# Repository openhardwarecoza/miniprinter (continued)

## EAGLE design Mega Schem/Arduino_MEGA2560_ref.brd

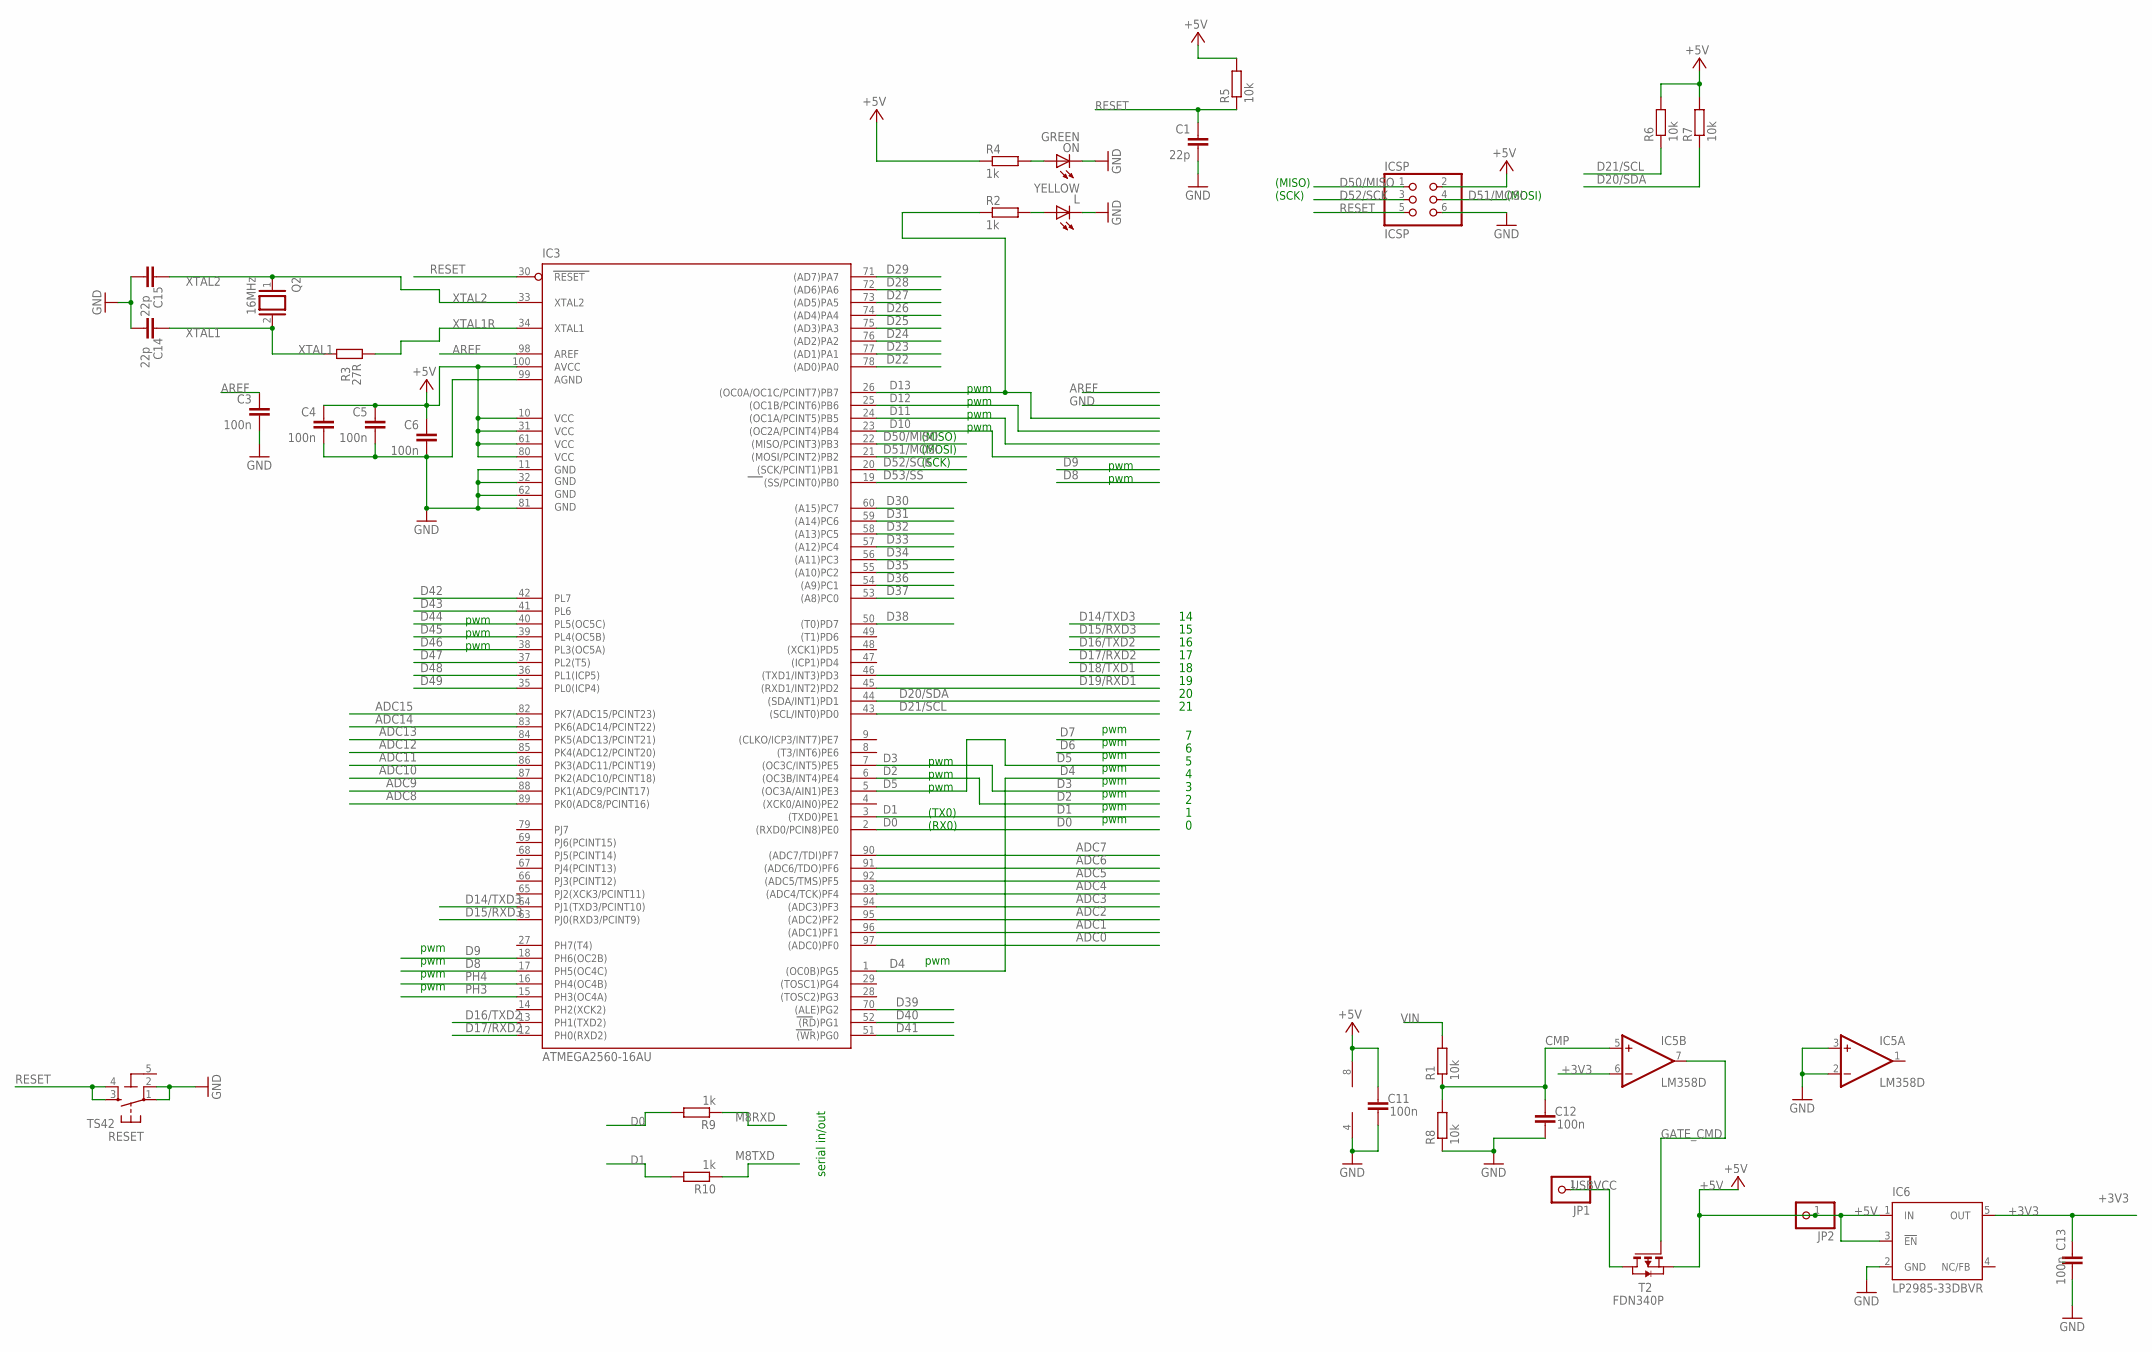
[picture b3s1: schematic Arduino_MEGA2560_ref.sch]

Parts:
C1, C14, C15: 22p; C0603-ROUND
C3, C4, C5, C6, C12, C13: 100n; C0603-ROUND
C11: 100n; C0603
IC3: ATMEGA2560-16AU; TQFP100
IC5: LM358D; SO08
IC6: LP2985-33DBVR; SOT23-DBV
ICSP: ICSP; 2X03
JP1, JP2: PINHD-1X1; 1X01
L: YELLOW; CHIP-LED0805
ON: GREEN; CHIP-LED0805
Q2: 16MHz; QS
R1, R5, R6, R7, R8: 10k; R0603
R2, R4, R9, R10: 1k; R0603
R3: 27R; R0603-ROUND
RESET: TS42
T2: FDN340P; SOT-23

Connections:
5-GND: RESET.5 (5-GND)
+3V3: C13.2, IC5.6 (-IN), IC6.5 (OUT)
+5V: C4.1, C5.1, C6.1, C11.2, IC3.10 (VCC), IC3.31 (VCC1), IC3.61 (VCC2), IC3.80 (VCC3), IC3.100 (AVCC), IC5.8 (V+), IC6.1 (IN), IC6.3 (!EN), ICSP.2, JP2.1, R4.1, R5.2, R6.2, R7.2, T2.2 (S)
ADC0: IC3.97 ((ADC0)PF0)
ADC1: IC3.96 ((ADC1)PF1)
ADC2: IC3.95 ((ADC2)PF2)
ADC3: IC3.94 ((ADC3)PF3)
ADC4: IC3.93 ((ADC4/TCK)PF4)
ADC5: IC3.92 ((ADC5/TMS)PF5)
ADC6: IC3.91 ((ADC6/TDO)PF6)
ADC7: IC3.90 ((ADC7/TDI)PF7)
ADC8: IC3.89 (PK0(ADC8/PCINT16))
ADC9: IC3.88 (PK1(ADC9/PCINT17))
ADC10: IC3.87 (PK2(ADC10/PCINT18))
ADC11: IC3.86 (PK3(ADC11/PCINT19))
ADC12: IC3.85 (PK4(ADC12/PCINT20))
ADC13: IC3.84 (PK5(ADC13/PCINT21))
ADC14: IC3.83 (PK6(ADC14/PCINT22))
ADC15: IC3.82 (PK7(ADC15/PCINT23))
AREF: C3.1, IC3.98 (AREF)
CMP: C12.2, IC5.5 (+IN), R1.1, R8.2
D0: IC3.2 ((RXD0/PCIN8)PE0), R9.2
D1: IC3.3 ((TXD0)PE1), R10.2
D2: IC3.6 ((OC3B/INT4)PE4)
D3: IC3.7 ((OC3C/INT5)PE5)
D4: IC3.1 ((OC0B)PG5)
D5: IC3.5 ((OC3A/AIN1)PE3)
D8: IC3.17 (PH5(OC4C))
D9: IC3.18 (PH6(OC2B))
D10: IC3.23 ((OC2A/PCINT4)PB4)
D11: IC3.24 ((OC1A/PCINT5)PB5)
D12: IC3.25 ((OC1B/PCINT6)PB6)
D13: IC3.26 ((OC0A/OC1C/PCINT7)PB7), R2.1
D14/TXD3: IC3.64 (PJ1(TXD3/PCINT10))
D15/RXD3: IC3.63 (PJ0(RXD3/PCINT9))
D16/TXD2: IC3.13 (PH1(TXD2))
D17/RXD2: IC3.12 (PH0(RXD2))
D18/TXD1: IC3.46 ((TXD1/INT3)PD3)
D19/RXD1: IC3.45 ((RXD1/INT2)PD2)
D20/SDA: IC3.44 ((SDA/INT1)PD1), R7.1
D21/SCL: IC3.43 ((SCL/INT0)PD0), R6.1
D22: IC3.78 ((AD0)PA0)
D23: IC3.77 ((AD1)PA1)
D24: IC3.76 ((AD2)PA2)
D25: IC3.75 ((AD3)PA3)
D26: IC3.74 ((AD4)PA4)
D27: IC3.73 ((AD5)PA5)
D28: IC3.72 ((AD6)PA6)
D29: IC3.71 ((AD7)PA7)
D30: IC3.60 ((A15)PC7)
D31: IC3.59 ((A14)PC6)
D32: IC3.58 ((A13)PC5)
D33: IC3.57 ((A12)PC4)
D34: IC3.56 ((A11)PC3)
D35: IC3.55 ((A10)PC2)
D36: IC3.54 ((A9)PC1)
D37: IC3.53 ((A8)PC0)
D38: IC3.50 ((T0)PD7)
D39: IC3.70 ((ALE)PG2)
D40: IC3.52 ((RD)PG1)
D41: IC3.51 ((WR)PG0)
D42: IC3.42 (PL7)
D43: IC3.41 (PL6)
D44: IC3.40 (PL5(OC5C))
D45: IC3.39 (PL4(OC5B))
D46: IC3.38 (PL3(OC5A))
D47: IC3.37 (PL2(T5))
D48: IC3.36 (PL1(ICP5))
D49: IC3.35 (PL0(ICP4))
D50/MISO: IC3.22 ((MISO/PCINT3)PB3), ICSP.1
D51/MOSI: IC3.21 ((MOSI/PCINT2)PB2), ICSP.4
D52/SCK: IC3.20 ((SCK/PCINT1)PB1), ICSP.3
D53/SS: IC3.19 ((SS/PCINT0)PB0)
GATE_CMD: IC5.7 (OUT), T2.3 (G)
GND: C1.2, C3.2, C4.2, C5.2, C6.2, C11.1, C12.1, C13.1, C14.1, C15.1, IC3.11 (GND), IC3.32 (GND1), IC3.62 (GND2), IC3.81 (GND3), IC3.99 (AGND), IC5.2 (-IN), IC5.3 (+IN), IC5.4 (V-), IC6.2 (GND), ICSP.6, L.C, ON.C, R8.1, RESET.1, RESET.2
M8RXD: R9.1
M8TXD: R10.1
unnamed: L.A, R2.2
unnamed: ON.A, R4.2
PH3: IC3.15 (PH3(OC4A))
PH4: IC3.16 (PH4(OC4B))
RESET: C1.1, IC3.30 (RESET), ICSP.5, R5.1, RESET.3, RESET.4
USBVCC: JP1.1, T2.1 (D)
VIN: R1.2
XTAL1: C14.2, Q2.2, R3.2
XTAL1R: IC3.34 (XTAL1), R3.1
XTAL2: C15.2, IC3.33 (XTAL2), Q2.1

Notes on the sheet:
(SCK)
(MISO)
(MOSI)
pwm
(TX0)
(RX0)
serial in/out

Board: 2 copper layers, 31 parts (0 on the bottom side), 21 nets, no tracks yet.

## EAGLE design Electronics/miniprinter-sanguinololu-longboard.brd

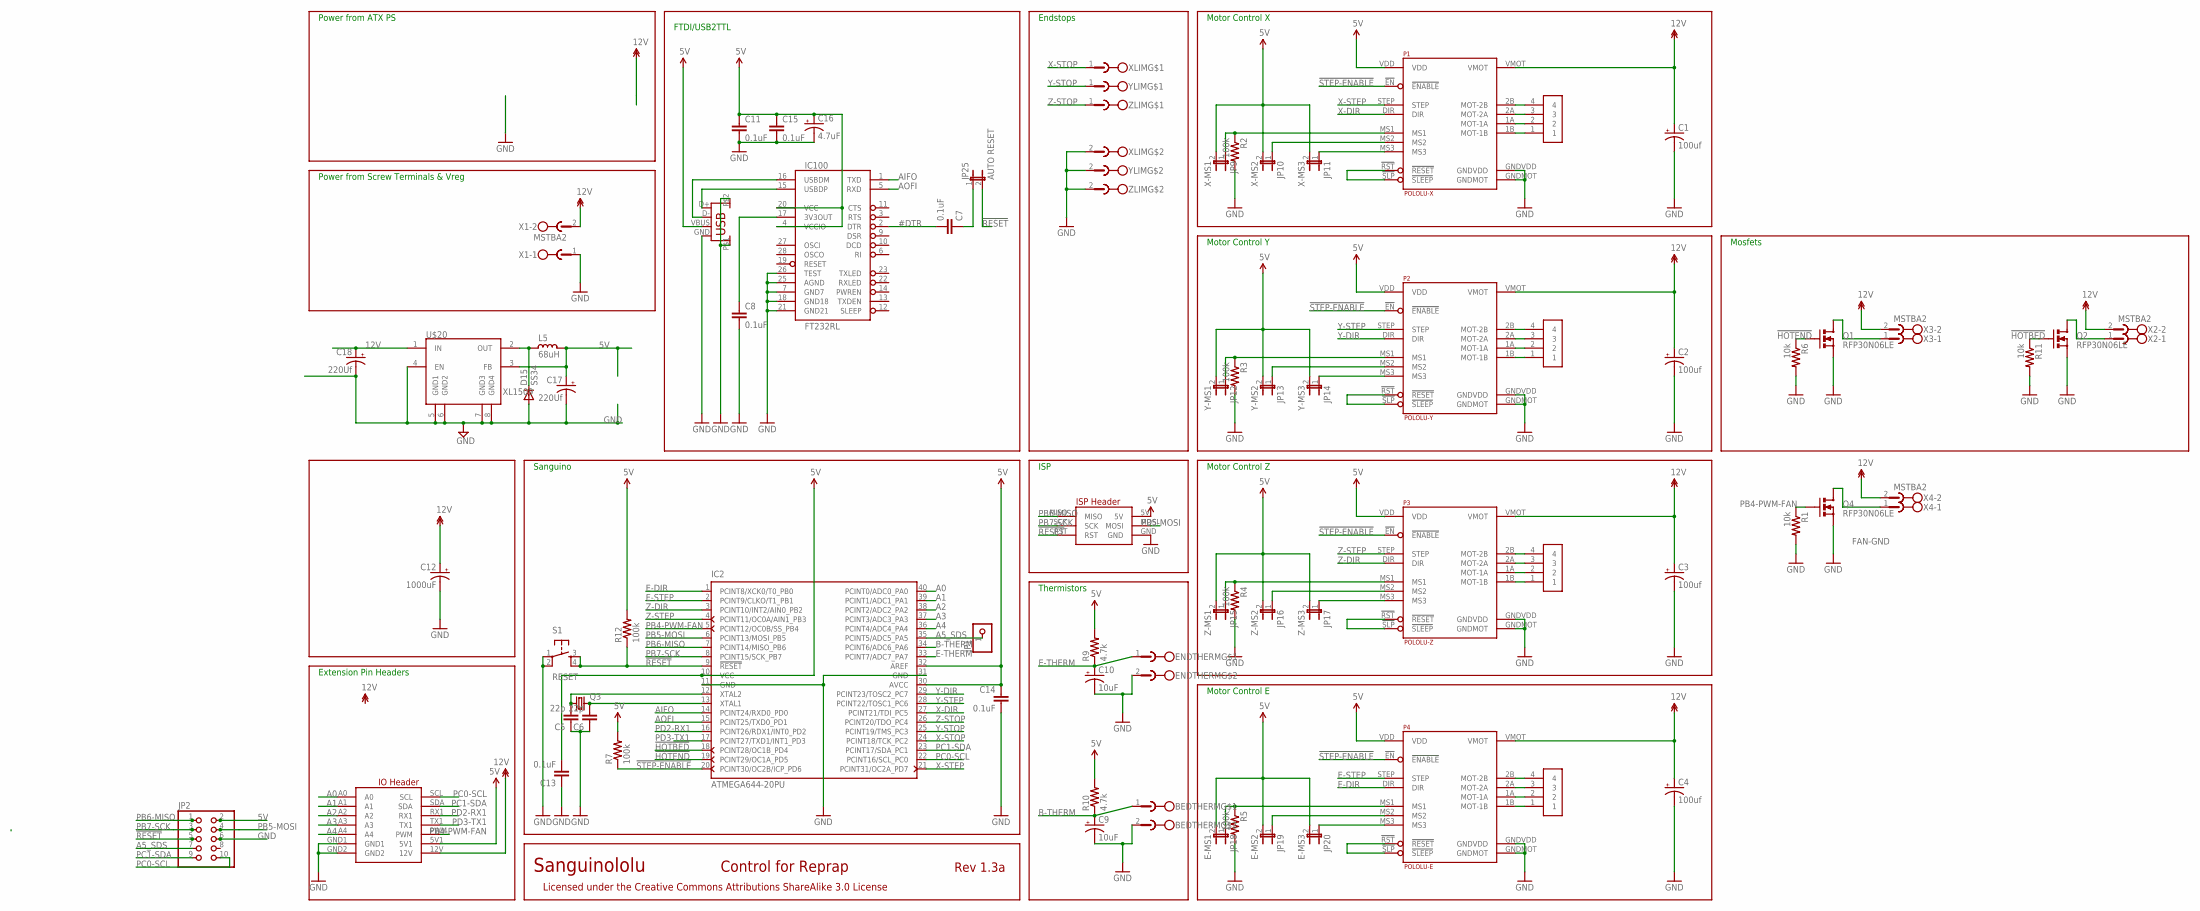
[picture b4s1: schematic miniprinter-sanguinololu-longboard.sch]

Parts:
BEDTHERM: Phoenix Pluggable 3.81mm 2 way; MC1.5/2-G-3.81
C1, C2, C3, C4: 100uf; CPOL-RADIAL-100UF-25V
C5, C6: 22p; CAP-PTH-SMALL2
C7, C8, C11, C13, C14, C15: 0.1uF; CAP-PTH-SMALL2
C9, C10: 10uF; CPOL-RADIAL-10UF-25V
C12: 1000uF; CPOL-RADIAL-1000UF-25V
C16: 4.7uF; CPOL-RADIAL-10UF-25V
C17, C18: 220Uf; CPOL-RADIAL-100UF-25V
D15: SS34; DO-214AC
ENDTHERM: Phoenix Pluggable 3.81mm 2 way; MC1.5/2-G-3.81
IC2: ATMEGA644-20PU; DIL40
IC100: FT232RL; SSOP28DB
J1: USB; USB-B-PTH
JP1: PINHD-1X1; 1X01
JP2: PINHD-2X5; 2X05
JP9: X-MS1; 1X02
JP10: X-MS2; 1X02
JP11: X-MS3; 1X02
JP12: Y-MS1; 1X02
JP13: Y-MS2; 1X02
JP14: Y-MS3; 1X02
JP15: Z-MS1; 1X02
JP16: Z-MS2; 1X02
JP17: Z-MS3; 1X02
JP18: E-MS1; 1X02
JP19: E-MS2; 1X02
JP20: E-MS3; 1X02
JP25: AUTO RESET; 1X02
L5: 68uH; CD75
P1: POLOLU-X; POLOLU-ALLEGRO-PTH
P2: POLOLU-Y; POLOLU-ALLEGRO-PTH
P3: POLOLU-Z; POLOLU-ALLEGRO-PTH
P4: POLOLU-E; POLOLU-ALLEGRO-PTH
Q1, Q2, Q4: RFP30N06LE; TO220V
Q3: CRYSTALHC49S; HC49/S
R1, R6, R11: 10k; AXIAL-0.3
R2, R3, R4, R5, R7, R12: 100k; AXIAL-0.3
R9, R10: 4.7k; AXIAL-0.3
S1: RESET; TACTILE-PTH
U$17, U$25, U$26, U$27: CONNECTOR-M4; 3.81MM-4WAY-PLUGGABLE-SCREW
U$20: XL1509; SO08
U$24: IO_HEADERS_SCREW; IO_HEADER-PLATEDSCREW
X1, X2, X3, X4: MSTBA2
XLIM: Phoenix Pluggable 3.81mm 2 way; MC1.5/2-G-3.81
YLIM: Phoenix Pluggable 3.81mm 2 way; MC1.5/2-G-3.81
ZLIM: Phoenix Pluggable 3.81mm 2 way; MC1.5/2-G-3.81

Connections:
3V3: C8.1, IC100.17 (3V3OUT)
5V: C11.1, C13.2, C14.1, C15.1, C16.1 (+), C17.1 (+), IC2.10 (VCC), IC2.30 (AVCC), IC2.32 (AREF), IC100.4 (VCCIO), IC100.20 (VCC), J1.VBUS, JP2.2, JP9.2, JP10.2, JP11.2, JP12.2, JP13.2, JP14.2, JP15.2, JP16.2, JP17.2, JP18.2, JP19.2, JP20.2, L5.1, P1.VDD, P2.VDD, P3.VDD, P4.VDD, R7.P$2 (2), R9.P$2 (2), R10.P$2 (2), R12.P$2 (2), U$20.3 (FB), U$24.5V, U$24.5V1
12V: C1.1 (+), C2.1 (+), C3.1 (+), C4.1 (+), C12.1 (+), C18.1 (+), P1.VMOT, P2.VMOT, P3.VMOT, P4.VMOT, U$20.1 (IN), U$24.12V, X1.2, X2.2, X3.2, X4.2
!FTDI-RESET: C7.1, JP25.1
!HOTBED: IC2.18 (PCINT28/OC1B_PD4), Q2.1 (G), R11.P$1 (1)
!HOTEND: IC2.19 (PCINT29/OC1A_PD5), Q1.1 (G), R6.P$1 (1)
!RESET: IC2.9 (!RESET), JP2.5, JP25.2, R12.P$1 (1), S1.3, S1.4, U$24.RST
!STEP-ENABLE: IC2.20 (PCINT30/OC2B/ICP_PD6), P1.!EN (!ENABLE), P2.!EN (!ENABLE), P3.!EN (!ENABLE), P4.!EN (!ENABLE), R7.P$1 (1)
#DTR: C7.2, IC100.2 (DTR)
A0: IC2.40 (PCINT0/ADC0_PA0), U$24.A0
A1: IC2.39 (PCINT1/ADC1_PA1), U$24.A1
A2: IC2.38 (PCINT2/ADC2_PA2), U$24.A2
A3: IC2.37 (PCINT3/ADC3_PA3), U$24.A3
A4: IC2.36 (PCINT4/ADC4_PA4), U$24.A4
A5_SDS: IC2.35 (PCINT5/ADC5_PA5), JP1.1, JP2.7
AIFO: IC2.14 (PCINT24/RXD0_PD0), IC100.1 (TXD)
AOFI: IC2.15 (PCINT25/TXD0_PD1), IC100.5 (RXD)
B-THERM: BEDTHERM.1, C9.1 (+), IC2.34 (PCINT6/ADC6_PA6), R10.P$1 (1)
E-DIR: IC2.1 (PCINT8/XCK0/T0_PB0), P4.DIR
E-MS1: JP18.1, P4.MS1, R5.P$1 (1)
E-MS2: JP19.1, P4.MS2
E-MS3: JP20.1, P4.MS3
E-RESETSLEEP: P4.!RST (!RESET), P4.!SLP (!SLEEP)
E-STEP: IC2.2 (PCINT9/CLKO/T1_PB1), P4.STEP
E-THERM: C10.1 (+), ENDTHERM.1, IC2.33 (PCINT7/ADC7_PA7), R9.P$1 (1)
FAN-GND: Q4.2 (D), X4.1
GND: BEDTHERM.2, C1.2 (-), C2.2 (-), C3.2 (-), C4.2 (-), C5.1, C6.1, C8.2, C9.2 (-), C10.2 (-), C11.2, C12.2 (-), C13.1, C14.2, C15.2, C16.2 (-), C17.2 (-), C18.2 (-), D15.2 (A), ENDTHERM.2, IC2.11 (GND), IC2.31 (GND), IC100.7 (GND7), IC100.18 (GND18), IC100.21 (GND21), IC100.25 (AGND), IC100.26 (TEST), J1.GND, J1.P$1, J1.P$2, JP2.6, P1.GNDMOT, P1.GNDVDD, P2.GNDMOT, P2.GNDVDD, P3.GNDMOT, P3.GNDVDD, P4.GNDMOT, P4.GNDVDD, Q1.3 (S), Q2.3 (S), Q4.3 (S), R1.P$2 (2), R2.P$2 (2), R3.P$2 (2), R4.P$2 (2), R5.P$2 (2), R6.P$2 (2), R11.P$2 (2), S1.1, S1.2, U$20.4 (EN), U$20.5 (GND1), U$20.6 (GND2), U$20.7 (GND3), U$20.8 (GND4), U$24.GND, U$24.GND1, U$24.GND2, X1.1, XLIM.2, YLIM.2, ZLIM.2
HOTBED-GND: Q2.2 (D), X2.1
HOTEND-GND: Q1.2 (D), X3.1
unnamed: P4.1B (MOT-1B), U$27.1
unnamed: P4.1A (MOT-1A), U$27.2
unnamed: P4.2A (MOT-2A), U$27.3
unnamed: P4.2B (MOT-2B), U$27.4
unnamed: P3.1B (MOT-1B), U$26.1
unnamed: P3.1A (MOT-1A), U$26.2
unnamed: P3.2A (MOT-2A), U$26.3
unnamed: P3.2B (MOT-2B), U$26.4
unnamed: P2.1B (MOT-1B), U$25.1
unnamed: P2.1A (MOT-1A), U$25.2
unnamed: P2.2A (MOT-2A), U$25.3
unnamed: P2.2B (MOT-2B), U$25.4
unnamed: P1.1B (MOT-1B), U$17.1
unnamed: P1.1A (MOT-1A), U$17.2
unnamed: P1.2A (MOT-2A), U$17.3
unnamed: P1.2B (MOT-2B), U$17.4
unnamed: D15.1 (C), L5.2, U$20.2 (OUT)
PB4-PWM-FAN: IC2.5 (PCINT12/OC0B/SS_PB4), Q4.1 (G), R1.P$1 (1), U$24.PWM
PB5-MOSI: IC2.6 (PCINT13/MOSI_PB5), JP2.4, U$24.MOSI
PB6-MISO: IC2.7 (PCINT14/MISO_PB6), JP2.1, U$24.MISO
PB7-SCK: IC2.8 (PCINT15/SCK_PB7), JP2.3, U$24.SCK
PC0-SCL: IC2.22 (PCINT16/SCL_PC0), JP2.10, U$24.SCL
PC1-SDA: IC2.23 (PCINT17/SDA_PC1), JP2.9, U$24.SDA
PD2-RX1: IC2.16 (PCINT26/RDX1/INT0_PD2), U$24.RX1
PD3-TX1: IC2.17 (PCINT27/TXD1/INT1_PD3), U$24.TX1
USBDM: IC100.16 (USBDM), J1.D-
USBDP: IC100.15 (USBDP), J1.D+
X-DIR: IC2.27 (PCINT21/TDI_PC5), P1.DIR
X-MS1: JP9.1, P1.MS1, R2.P$1 (1)
X-MS2: JP10.1, P1.MS2
X-MS3: JP11.1, P1.MS3
X-RESETSLEEP: P1.!RST (!RESET), P1.!SLP (!SLEEP)
X-STEP: IC2.21 (PCINT31/OC2A_PD7), P1.STEP
X-STOP: IC2.24 (PCINT18/TCK_PC2), XLIM.1
XTAL1: C6.2, IC2.13 (XTAL1), Q3.2
XTAL2: C5.2, IC2.12 (XTAL2), Q3.1
Y-DIR: IC2.29 (PCINT23/TOSC2_PC7), P2.DIR
Y-MS1: JP12.1, P2.MS1, R3.P$1 (1)
Y-MS2: JP13.1, P2.MS2
Y-MS3: JP14.1, P2.MS3
Y-RESETSLEEP: P2.!RST (!RESET), P2.!SLP (!SLEEP)
Y-STEP: IC2.28 (PCINT22/TOSC1_PC6), P2.STEP
Y-STOP: IC2.25 (PCINT19/TMS_PC3), YLIM.1
Z-DIR: IC2.3 (PCINT10/INT2/AIN0_PB2), P3.DIR
Z-MS1: JP15.1, P3.MS1, R4.P$1 (1)
Z-MS2: JP16.1, P3.MS2
Z-MS3: JP17.1, P3.MS3
Z-RESETSLEEP: P3.!RST (!RESET), P3.!SLP (!SLEEP)
Z-STEP: IC2.4 (PCINT11/OC0A/AIN1_PB3), P3.STEP
Z-STOP: IC2.26 (PCINT20/TDO_PC4), ZLIM.1

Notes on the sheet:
Motor Control X
Motor Control Y
Motor Control Z
Motor Control E
ISP
Thermistors
Endstops
Sanguino
FTDI/USB2TTL
Mosfets
Sanguinololu
Rev 1.3a
Control for Reprap
Licensed under the Creative Commons Attributions ShareAlike 3.0 License
Extension Pin Headers
Power from ATX PS
Power from Screw Terminals & Vreg

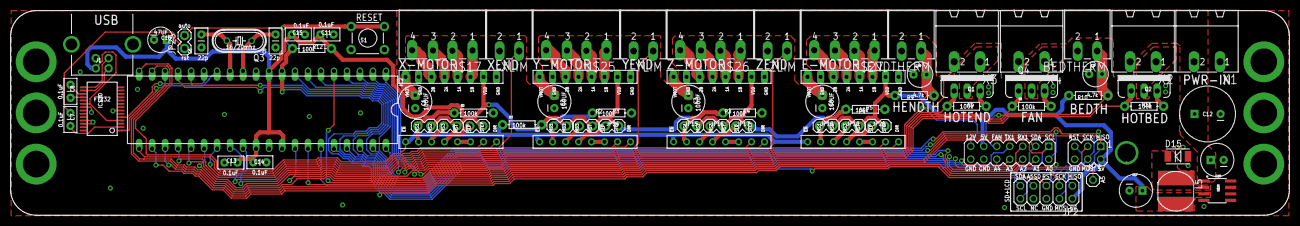
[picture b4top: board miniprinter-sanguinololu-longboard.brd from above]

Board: 2 copper layers, 250.0 x 40.0 mm, 73 parts (0 on the bottom side), 79 nets.

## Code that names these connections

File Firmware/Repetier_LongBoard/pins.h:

#ifndef PINS_H
#define PINS_H

/*
The board assignment defines the capabilities of the motherboard and the used pins.
Each board definition follows the following scheme:

CPU_ARCH
  ARCH_AVR for AVR based boards
  ARCH_ARM for all arm based boards

STEPPER_CURRENT_CONTROL
  CURRENT_CONTROL_MANUAL  1  // mechanical poti, default if not defined
  CURRENT_CONTROL_DIGIPOT 2  // Use a digipot like RAMBO does
  CURRENT_CONTROL_LTC2600 3  // Use LTC2600 like Foltyn 3D Master

*/

#define ARCH_AVR 1
#define ARCH_ARM 2

#define CURRENT_CONTROL_MANUAL  1  // mechanical poti, default if not defined
#define CURRENT_CONTROL_DIGIPOT 2  // Use a digipot like RAMBO does
#define CURRENT_CONTROL_LTC2600 3  // Use LTC2600 like Foltyn 3D Master

/***************************************************************************************
    OpenHardware.co.za FrontPrint Controller 1.0
****************************************************************************************/

// ATMEL ATMEGA644P / SANGUINO
//
//                   +--------\/--------+
//  INT0 (D 0) PB0  1|edir              |40  PA0 (AI 0 / D31)
//  INT1 (D 1) PB1  2|estp              |39  PA1 (AI 1 / D30)
//  INT2 (D 2) PB2  3|zdir              |38  PA2 (AI 2 / D29)
//   PWM (D 3) PB3  4|zstp              |37  PA3 (AI 3 / D28)
//   PWM (D 4) PB4  5|fan               |36  PA4 (AI 4 / D27)
//  MOSI (D 5) PB5  6|mosi           sds|35  PA5 (AI 5 / D26)
//  MISO (D 6) PB6  7|miso        btherm|34  PA6 (AI 6 / D25)
//   SCK (D 7) PB7  8|sck        etherm |33  PA7 (AI 7 / D24)
//             RST  9|reset         aref|32  AREF
//             VCC 10|5v             gnd|31  GND 
//             GND 11|gnd             5v|30  AVCC
//           XTAL2 12|xtal          ydir|29  PC7 (D 23)
//           XTAL1 13|xtal         ystep|28  PC6 (D 22)
//  RX0 (D 8)  PD0 14|rxd           xdir|27  PC5 (D 21) TDI
//  TX0 (D 9)  PD1 15|txd          zstop|26  PC4 (D 20) TDO
//  RX1 (D 10) PD2 16|rxd2         ystop|5  PC3 (D 19) TMS
//  TX1 (D 11) PD3 17|txd2         xstop|24  PC2 (D 18) TCK
//  PWM (D 12) PD4 18|hotbed         sda|23  PC1 (D 17) SDA
//  PWM (D 13) PD5 19|hotend         scl|22  PC0 (D 16) SCL
//  PWM (D 14) PD6 20|enable        xstp|21  PD7 (D 15) PWM
//                   +------------------+

#if MOTHERBOARD == 73
#define KNOWN_BOARD 1

//#if !defined(AVR_ATmega644P) && !defined(AVR_ATmega644) && !defined(AVR_ATmega1284P)
//#error Oops! Make sure you have 'Gen7' selected from the 'Tools -> Boards' menu.
//#endif

//x axis pins
#define ORIG_X_STEP_PIN 15
#define ORIG_X_DIR_PIN 21
#define ORIG_X_ENABLE_PIN 14
#define ORIG_X_MIN_PIN 18
#define ORIG_X_MAX_PIN -1

//y axis pins
#define ORIG_Y_STEP_PIN 22
#define ORIG_Y_DIR_PIN 23
#define ORIG_Y_ENABLE_PIN 14
#define ORIG_Y_MIN_PIN 19
#define ORIG_Y_MAX_PIN -1

//z axis pins
#define ORIG_Z_STEP_PIN 3
#define ORIG_Z_DIR_PIN 2
#define ORIG_Z_ENABLE_PIN 14
#define ORIG_Z_MIN_PIN 20
#define ORIG_Z_MAX_PIN -1

//First extruder pins
#define ORIG_E0_STEP_PIN 1
#define ORIG_E0_DIR_PIN 0
#define ORIG_E0_ENABLE_PIN 14
#define TEMP_0_PIN 7
#define HEATER_0_PIN 13

//Second Extruder pins
//#define ORIG_E1_STEP_PIN -1//20
//#define ORIG_E1_DIR_PIN -1//18
//#define ORIG_E1_ENABLE_PIN -1//25
//#define TEMP_2_PIN -1
//#define HEATER_2_PIN -1

//Heated Bed Pins
#define TEMP_1_PIN 6
#define HEATER_1_PIN 12

//SD Card Pins
#define SDPOWER -1
#define SDSS 26
#define SCK_PIN 7
#define MISO_PIN 6
#define MOSI_PIN 5

#define ORIG_FAN_PIN 4//FAN and ATX Power Supply Control Pins
#define PS_ON_PIN -1

#define LED_PIN -1
#define SDSUPPORT true  // sd card reader on board
#define SDCARDDETECT -1

#define E0_PINS ORIG_E0_STEP_PIN,ORIG_E0_DIR_PIN,ORIG_E0_ENABLE_PIN,
#define E1_PINS ORIG_E1_STEP_PIN,ORIG_E1_DIR_PIN,ORIG_E1_ENABLE_PIN,
#endif

#ifndef CPU_ARCH  // Set default architecture
#define CPU_ARCH ARCH_AVR
#endif

#ifndef SDSSORIG
#define SDSSORIG -1
#endif

#ifndef STEPPER_CURRENT_CONTROL // Set default stepper current control if not set yet.
#define STEPPER_CURRENT_CONTROL  CURRENT_CONTROL_MANUAL
#endif

#ifndef FAN_BOARD_PIN
#define FAN_BOARD_PIN -1
#endif

#if NUM_EXTRUDER==1
#define E1_PINS
#endif

#if NUM_EXTRUDER<3
#define E2_PINS
#endif

#ifndef HEATER_PINS_INVERTED
#define HEATER_PINS_INVERTED 0
#endif

// Original pin assignmats to be used in configuration tool
#define X_STEP_PIN ORIG_X_STEP_PIN
#define X_DIR_PIN ORIG_X_DIR_PIN
#define X_ENABLE_PIN ORIG_X_ENABLE_PIN
#define X_MIN_PIN ORIG_X_MIN_PIN
#define X_MAX_PIN ORIG_X_MAX_PIN

#define Y_STEP_PIN ORIG_Y_STEP_PIN
#define Y_DIR_PIN ORIG_Y_DIR_PIN
#define Y_ENABLE_PIN ORIG_Y_ENABLE_PIN
#define Y_MIN_PIN ORIG_Y_MIN_PIN
#define Y_MAX_PIN ORIG_Y_MAX_PIN

#define Z_STEP_PIN ORIG_Z_STEP_PIN
#define Z_DIR_PIN ORIG_Z_DIR_PIN
#define Z_ENABLE_PIN ORIG_Z_ENABLE_PIN
#define Z_MIN_PIN ORIG_Z_MIN_PIN
#define Z_MAX_PIN ORIG_Z_MAX_PIN

#define E0_STEP_PIN ORIG_E0_STEP_PIN
#define E0_DIR_PIN ORIG_E0_DIR_PIN
#define E0_ENABLE_PIN ORIG_E0_ENABLE_PIN

#define E1_STEP_PIN ORIG_E1_STEP_PIN
#define E1_DIR_PIN ORIG_E1_DIR_PIN
#define E1_ENABLE_PIN ORIG_E1_ENABLE_PIN

#define E2_STEP_PIN ORIG_E2_STEP_PIN
#define E2_DIR_PIN ORIG_E2_DIR_PIN
#define E2_ENABLE_PIN ORIG_E2_ENABLE_PIN

#define E3_STEP_PIN ORIG_E3_STEP_PIN
#define E3_DIR_PIN ORIG_E3_DIR_PIN
#define E3_ENABLE_PIN ORIG_E3_ENABLE_PIN

#define E4_STEP_PIN ORIG_E4_STEP_PIN
#define E4_DIR_PIN ORIG_E4_DIR_PIN
#define E4_ENABLE_PIN ORIG_E4_ENABLE_PIN

#define E5_STEP_PIN ORIG_E5_STEP_PIN
#define E5_DIR_PIN ORIG_E5_DIR_PIN
#define E5_ENABLE_PIN ORIG_E5_ENABLE_PIN

#define FAN_PIN ORIG_FAN_PIN
#define FAN2_PIN ORIG_FAN2_PIN


#define SENSITIVE_PINS {0, 1, ORIG_X_STEP_PIN, ORIG_X_DIR_PIN, ORIG_X_ENABLE_PIN, ORIG_X_MIN_PIN, ORIG_X_MAX_PIN, \
        ORIG_Y_STEP_PIN, ORIG_Y_DIR_PIN, ORIG_Y_ENABLE_PIN, ORIG_Y_MIN_PIN, ORIG_Y_MAX_PIN, ORIG_Z_STEP_PIN,\
        ORIG_Z_DIR_PIN, ORIG_Z_ENABLE_PIN, ORIG_Z_MIN_PIN, ORIG_Z_MAX_PIN, LED_PIN, PS_ON_PIN, \
        HEATER_0_PIN, HEATER_1_PIN, ORIG_FAN_PIN, E0_PINS E1_PINS E2_PINS TEMP_0_PIN, TEMP_1_PIN,SDSS }
#endif

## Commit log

2019-12-18 PCB plates starting
2020-03-07 pcb plates 1
2020-08-28 proto2
2020-09-21 working firmware
